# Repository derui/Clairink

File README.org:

* Clairink
This is a split keyboard having these features:

- ZMK firmware
- 3D printed keyboard case & Rotally encoder nob
  - You can manage behavior with ZMK
- Focus Thocky sound with the Lofree's Phantom switch
- all wireless
- able to use rechageable AAA battery x2
  - I use eneloop for this

* Bill Of Materials

| Name                                   | Qty |
|----------------------------------------+-----|
| SeeedStudio XIAO nRF52480              |   2 |
| AAA battery holder                     |   4 |
| M2 nut                                 |  12 |
| M2 screw                               |  12 |
| AE-XCL102D333CR-G                      |   2 |
| 1N4148W                                |  64 |
| Choc V2 Socket                         |  42 |
| Rotally Encoder (ALPS EC12 compatible) |   2 |
| SS-12D01G3                             |   2 |
| chip condenser (0.1uF)                 |   4 |
| chip register (2.2KΩ)                  |   4 |

* LICENSE
MIT

** LICENSE note
This keyboard uses Seeed Studio's XIAO nRF52480 kicad symbol and footprint. There are licensed under MIT that they written in [[https://wiki.seeedstudio.com/ja/License/][here]].

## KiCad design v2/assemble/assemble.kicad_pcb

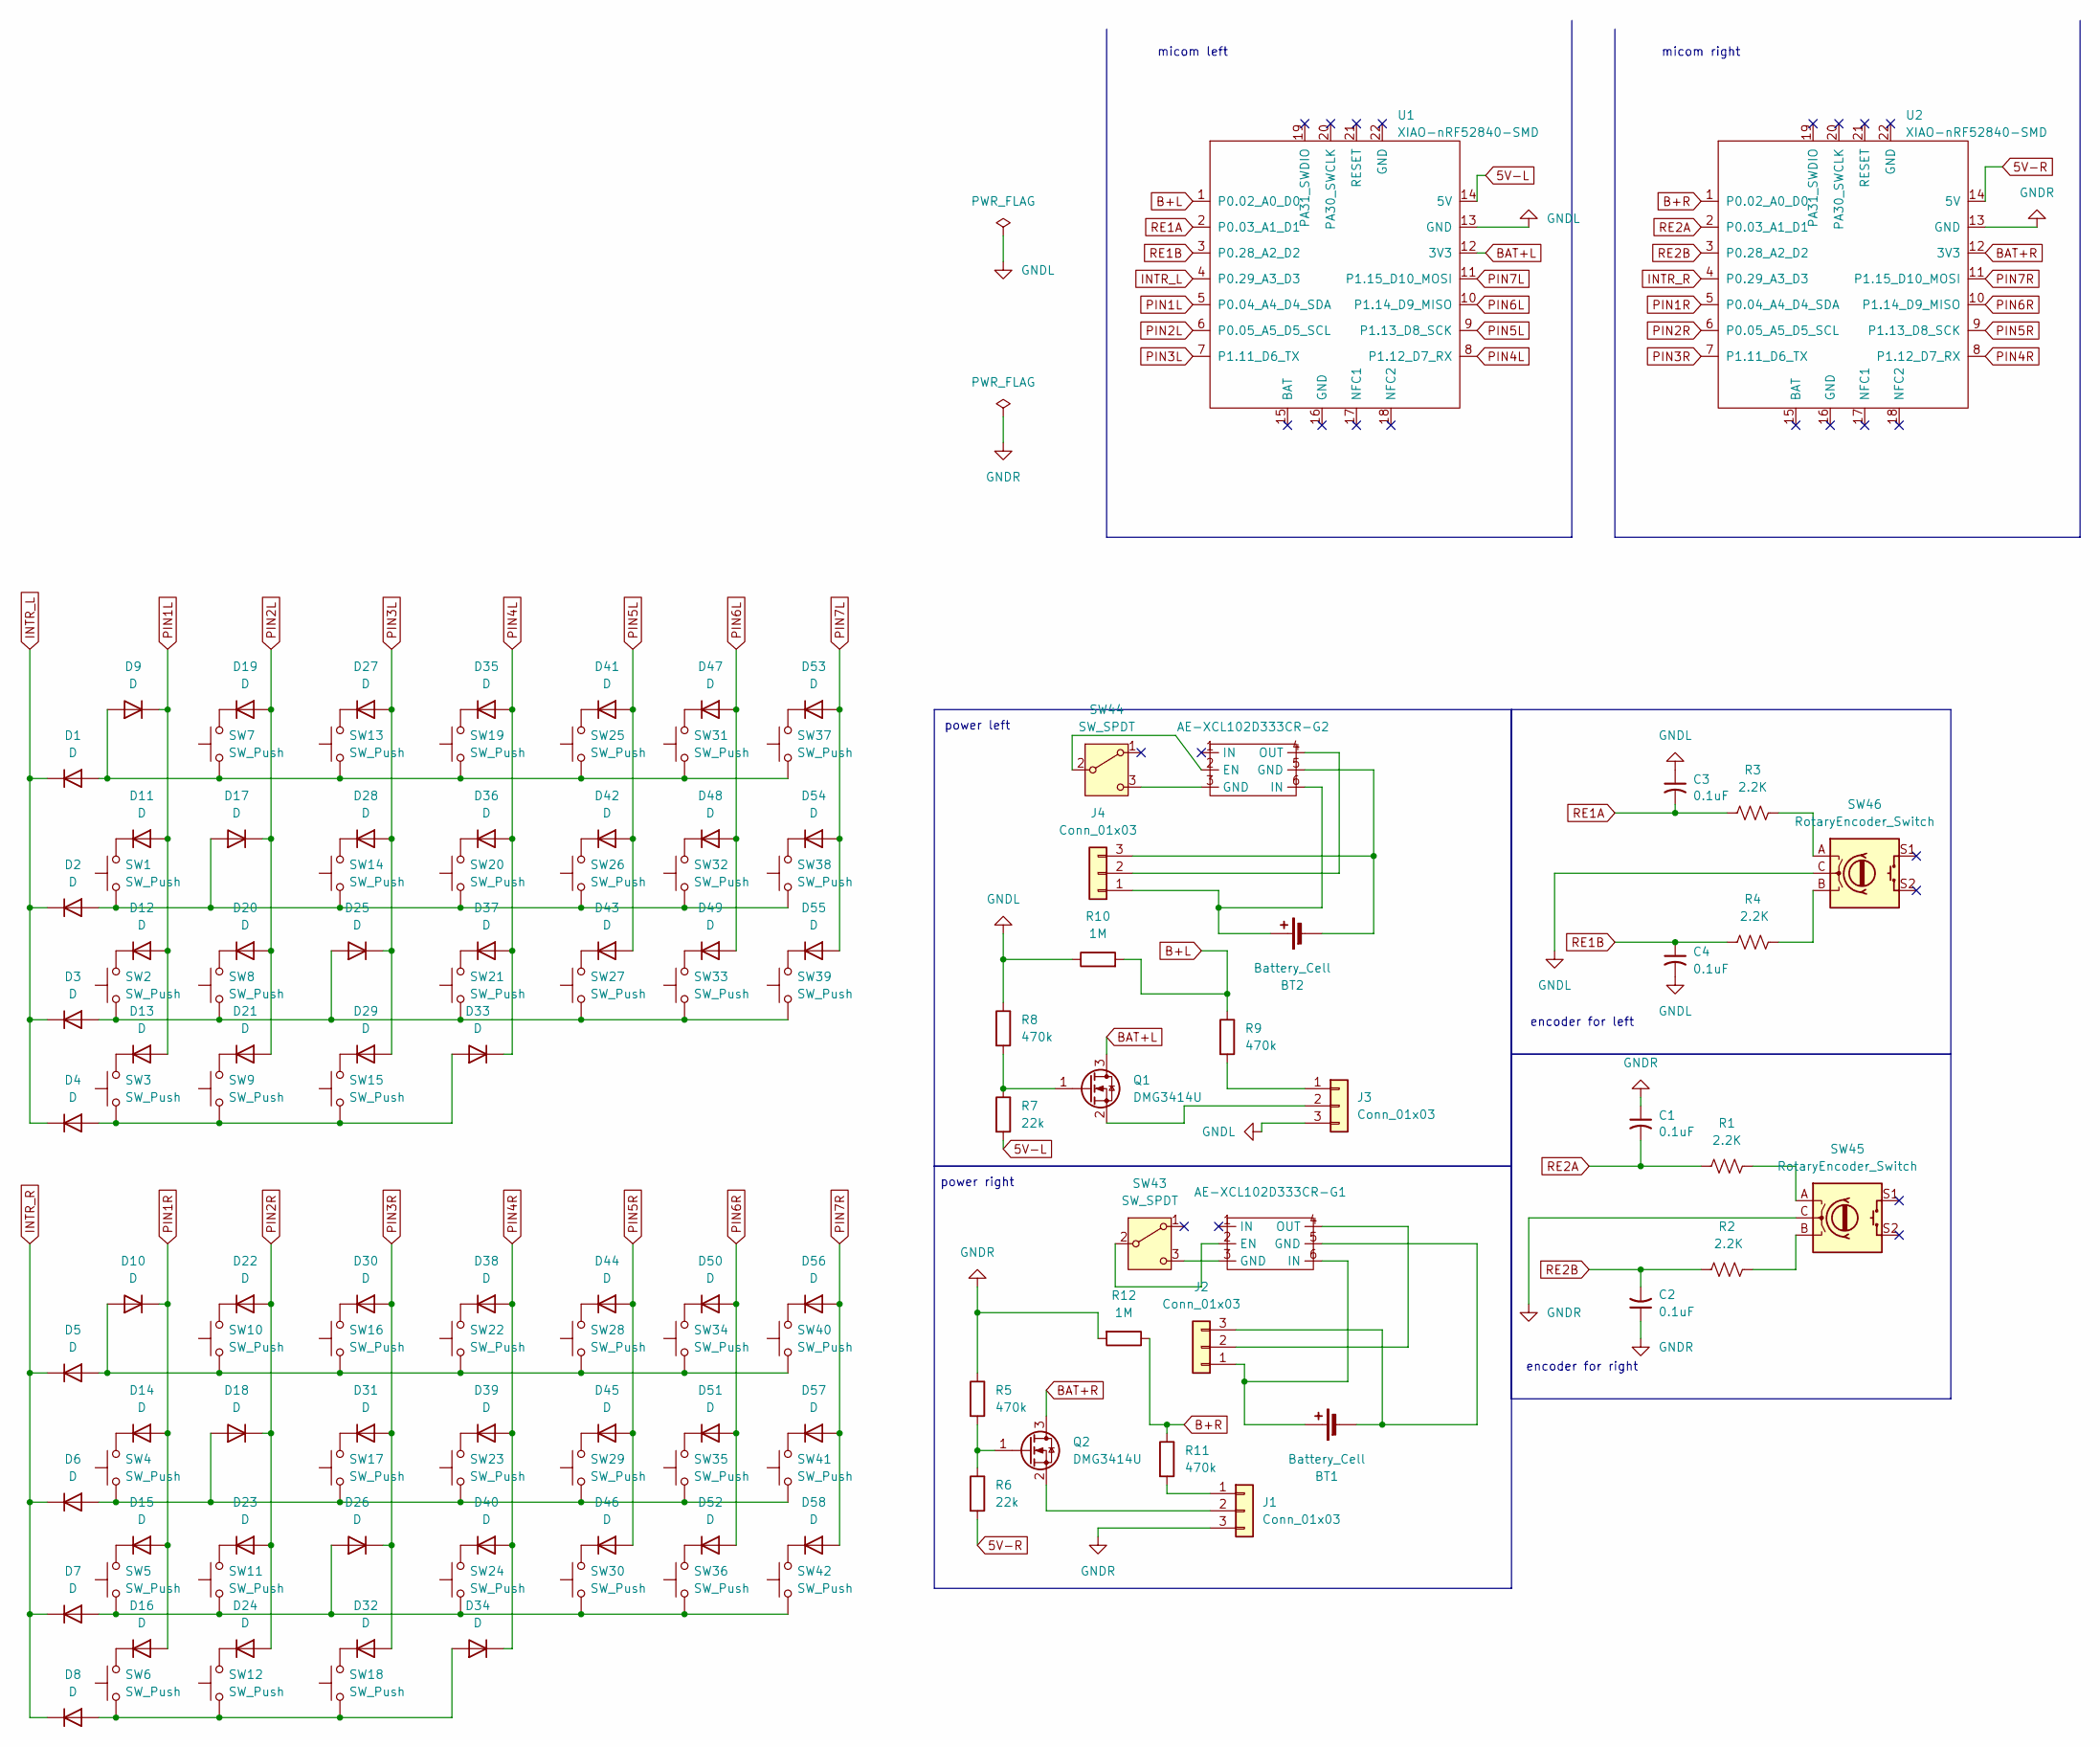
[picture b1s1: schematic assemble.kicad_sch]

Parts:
AE-XCL102D333CR-G1, AE-XCL102D333CR-G2: AE-XCL102D333CR-G
BT1, BT2: Battery_Cell; Battery_AAA
C1, C2, C3, C4: 0.1uF; C_0603_1608Metric_Pad1.08x0.95mm_HandSolder
D1, D2, D3, D4, D5, D6, D7, D8, D9, D10, D11, D12, D13, D14, D15, D16, D17, D18, D19, D20, D21, D22, D23, D24, D25, D26, D27, D28, D29, D30, D31, D32, D33, D34, D35, D36, D37, D38, D39, D40, D41, D42, D43, D44, D45, D46, D47, D48, D49, D50, D51, D52, D53, D54, D55, D56, D57, D58: D; Diode_SMD
J1, J2, J3, J4: Conn_01x03; JST_ZH_B3B-ZR_1x03_P1.50mm_Vertical
Q1, Q2: DMG3414U; SOT-23
R1, R2, R3, R4: 2.2K; R_0805_2012Metric_Pad1.20x1.40mm_HandSolder
R5, R8, R9, R11: 470k; R_0805_2012Metric_Pad1.20x1.40mm_HandSolder
R6, R7: 22k; R_0805_2012Metric_Pad1.20x1.40mm_HandSolder
R10, R12: 1M; R_0805_2012Metric_Pad1.20x1.40mm_HandSolder
SW1, SW2, SW3, SW4, SW5, SW6, SW7, SW8, SW9, SW10, SW11, SW12, SW13, SW14, SW15, SW16, SW17, SW18, SW19, SW20, SW21, SW22, SW23, SW24, SW25, SW26, SW27, SW28, SW29, SW30, SW31, SW32, SW33, SW34, SW35, SW36, SW37, SW38, SW39, SW40, SW41, SW42: SW_Push; Choc_v2_Hotswap_1u_16.6
SW43, SW44: SW_SPDT; TGSW_MSK-12D19
SW45, SW46: RotaryEncoder_Switch; RotaryEncoder_EC12E
U1, U2: XIAO-nRF52840-SMD

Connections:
5V-L: R7.2, U1.14 (5V)
5V-R: R6.2, U2.14 (5V)
B+L: R9.1, R10.2, U1.1 (P0.02_A0_D0)
B+R: R11.1, R12.1, U2.1 (P0.02_A0_D0)
BAT+L: Q1.3 (D), U1.12 (3V3)
BAT+R: Q2.3 (D), U2.12 (3V3)
GNDL: C3.1, C4.2, J3.3, R8.1, R10.1, SW46.C, U1.13 (GND)
GNDR: C1.1, C2.1, J1.3, R5.1, R12.2, SW45.C, U2.13 (GND)
INTR_L: D1.1 (K), D2.1 (K), D3.1 (K), D4.1 (K), U1.4 (P0.29_A3_D3)
INTR_R: D5.1 (K), D6.1 (K), D7.1 (K), D8.1 (K), U2.4 (P0.29_A3_D3)
unnamed: AE-XCL102D333CR-G1.2 (EN), SW43.2 (B)
unnamed: AE-XCL102D333CR-G1.4 (OUT), J2.2
unnamed: AE-XCL102D333CR-G2.2 (EN), SW44.2 (B)
unnamed: AE-XCL102D333CR-G2.4 (OUT), J4.2
unnamed: AE-XCL102D333CR-G1.6 (IN), BT1.1 (+), J2.1
unnamed: AE-XCL102D333CR-G1.5 (GND), BT1.2 (-), J2.3
unnamed: AE-XCL102D333CR-G2.6 (IN), BT2.1 (+), J4.1
unnamed: AE-XCL102D333CR-G2.5 (GND), BT2.2 (-), J4.3
unnamed: D1.2 (A), D9.2 (A), SW7.1, SW13.1, SW19.1, SW25.1, SW31.1, SW37.1
unnamed: D5.2 (A), D10.2 (A), SW10.1, SW16.1, SW22.1, SW28.1, SW34.1, SW40.1
unnamed: D11.1 (K), SW1.2
unnamed: D12.1 (K), SW2.2
unnamed: D13.1 (K), SW3.2
unnamed: D14.1 (K), SW4.2
unnamed: D15.1 (K), SW5.2
unnamed: D16.1 (K), SW6.2
unnamed: D2.2 (A), D17.2 (A), SW1.1, SW14.1, SW20.1, SW26.1, SW32.1, SW38.1
unnamed: D6.2 (A), D18.2 (A), SW4.1, SW17.1, SW23.1, SW29.1, SW35.1, SW41.1
unnamed: D19.1 (K), SW7.2
unnamed: D20.1 (K), SW8.2
unnamed: D21.1 (K), SW9.2
unnamed: D22.1 (K), SW10.2
unnamed: D23.1 (K), SW11.2
unnamed: D24.1 (K), SW12.2
unnamed: D3.2 (A), D25.2 (A), SW2.1, SW8.1, SW21.1, SW27.1, SW33.1, SW39.1
unnamed: D7.2 (A), D26.2 (A), SW5.1, SW11.1, SW24.1, SW30.1, SW36.1, SW42.1
unnamed: D27.1 (K), SW13.2
unnamed: D28.1 (K), SW14.2
unnamed: D29.1 (K), SW15.2
unnamed: D30.1 (K), SW16.2
unnamed: D31.1 (K), SW17.2
unnamed: D32.1 (K), SW18.2
unnamed: D4.2 (A), D33.2 (A), SW3.1, SW9.1, SW15.1
unnamed: D8.2 (A), D34.2 (A), SW6.1, SW12.1, SW18.1
unnamed: D35.1 (K), SW19.2
unnamed: D36.1 (K), SW20.2
unnamed: D37.1 (K), SW21.2
unnamed: D38.1 (K), SW22.2
unnamed: D39.1 (K), SW23.2
unnamed: D40.1 (K), SW24.2
unnamed: D41.1 (K), SW25.2
unnamed: D42.1 (K), SW26.2
unnamed: D43.1 (K), SW27.2
unnamed: D44.1 (K), SW28.2
unnamed: D45.1 (K), SW29.2
unnamed: D46.1 (K), SW30.2
unnamed: D47.1 (K), SW31.2
unnamed: D48.1 (K), SW32.2
unnamed: D49.1 (K), SW33.2
unnamed: D50.1 (K), SW34.2
unnamed: D51.1 (K), SW35.2
unnamed: D52.1 (K), SW36.2
unnamed: D53.1 (K), SW37.2
unnamed: D54.1 (K), SW38.2
unnamed: D55.1 (K), SW39.2
unnamed: D56.1 (K), SW40.2
unnamed: D57.1 (K), SW41.2
unnamed: D58.1 (K), SW42.2
unnamed: J1.1, R11.2
unnamed: J1.2, Q2.2 (S)
unnamed: J3.1, R9.2
unnamed: J3.2, Q1.2 (S)
unnamed: Q1.1 (G), R7.1, R8.2
unnamed: Q2.1 (G), R5.2, R6.1
unnamed: R1.2, SW45.A
unnamed: R2.2, SW45.B
unnamed: R3.2, SW46.A
unnamed: R4.2, SW46.B
unnamed: AE-XCL102D333CR-G1.3 (GND), SW43.3 (C)
unnamed: AE-XCL102D333CR-G2.3 (GND), SW44.3 (C)
PIN1L: D9.1 (K), D11.2 (A), D12.2 (A), D13.2 (A), U1.5 (P0.04_A4_D4_SDA)
PIN1R: D10.1 (K), D14.2 (A), D15.2 (A), D16.2 (A), U2.5 (P0.04_A4_D4_SDA)
PIN2L: D17.1 (K), D19.2 (A), D20.2 (A), D21.2 (A), U1.6 (P0.05_A5_D5_SCL)
PIN2R: D18.1 (K), D22.2 (A), D23.2 (A), D24.2 (A), U2.6 (P0.05_A5_D5_SCL)
PIN3L: D25.1 (K), D27.2 (A), D28.2 (A), D29.2 (A), U1.7 (P1.11_D6_TX)
PIN3R: D26.1 (K), D30.2 (A), D31.2 (A), D32.2 (A), U2.7 (P1.11_D6_TX)
PIN4L: D33.1 (K), D35.2 (A), D36.2 (A), D37.2 (A), U1.8 (P1.12_D7_RX)
PIN4R: D34.1 (K), D38.2 (A), D39.2 (A), D40.2 (A), U2.8 (P1.12_D7_RX)
PIN5L: D41.2 (A), D42.2 (A), D43.2 (A), U1.9 (P1.13_D8_SCK)
PIN5R: D44.2 (A), D45.2 (A), D46.2 (A), U2.9 (P1.13_D8_SCK)
PIN6L: D47.2 (A), D48.2 (A), D49.2 (A), U1.10 (P1.14_D9_MISO)
PIN6R: D50.2 (A), D51.2 (A), D52.2 (A), U2.10 (P1.14_D9_MISO)
PIN7L: D53.2 (A), D54.2 (A), D55.2 (A), U1.11 (P1.15_D10_MOSI)
PIN7R: D56.2 (A), D57.2 (A), D58.2 (A), U2.11 (P1.15_D10_MOSI)
RE1A: C3.2, R3.1, U1.2 (P0.03_A1_D1)
RE1B: C4.1, R4.1, U1.3 (P0.28_A2_D2)
RE2A: C1.2, R1.1, U2.2 (P0.03_A1_D1)
RE2B: C2.2, R2.1, U2.3 (P0.28_A2_D2)

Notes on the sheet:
encoder for right
encoder for left
micom right
power left
power right
micom left

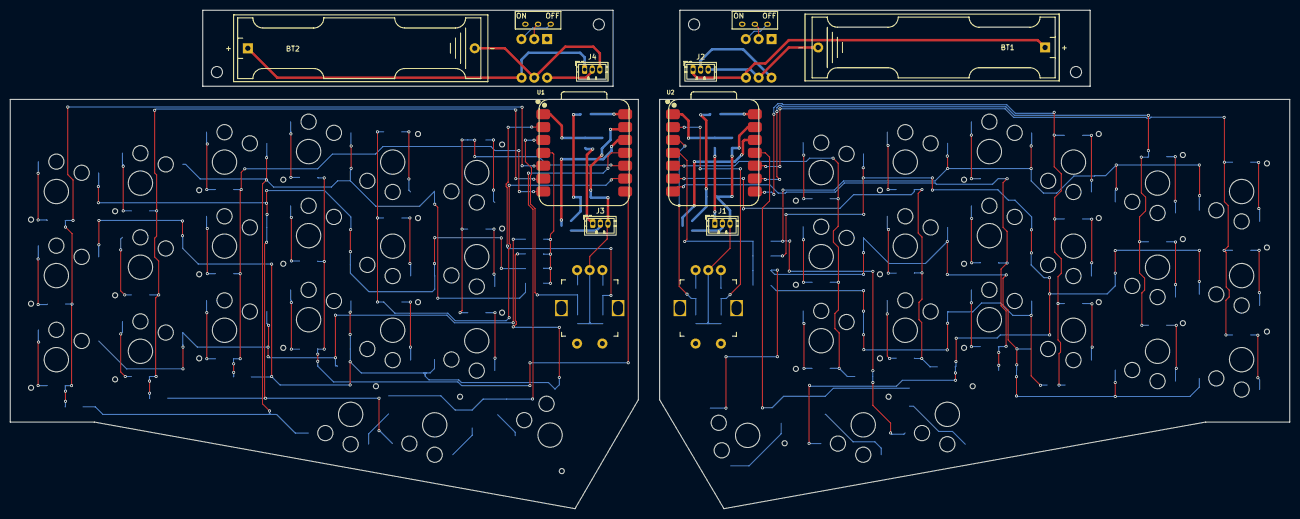
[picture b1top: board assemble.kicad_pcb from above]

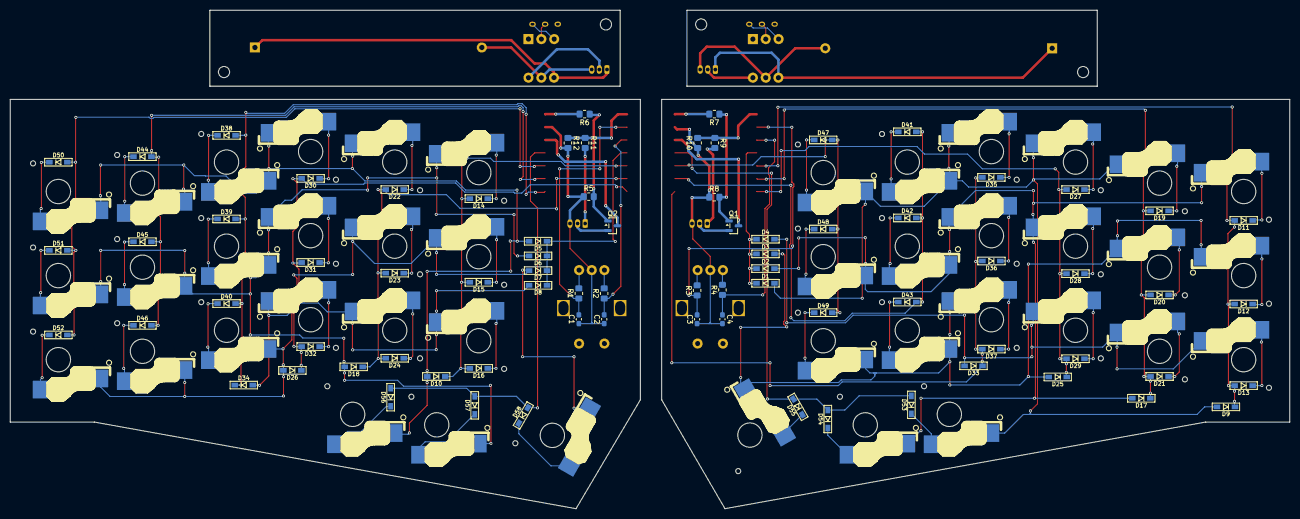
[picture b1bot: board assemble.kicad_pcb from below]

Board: 2 copper layers, 252.6 x 98.4 mm, 136 parts (18 on the bottom side), 98 nets.

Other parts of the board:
Ref**: Val**; m2_Screw_Hole
Ref**#2, Ref**#3, Ref**#4: Val**; m2_Screw_Hole

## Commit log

2026-03-08 feat: readme and base assembles
2026-03-09 feat: add some rotary encoder
2026-03-15 wip: implement PCB
2026-03-19 fix: move pcb
2026-03-23 fix: add screw hole
2026-03-27 chore: update flake
2026-03-29 fix: typo
2026-04-01 feat: add case base
2026-04-05 feat: add switch plate
2026-04-05 fix: add GND pattern
2026-04-05 fix: rename
2026-04-14 feat: update kicad
2026-05-13 feat: add v1.2 and v1.3
2026-05-16 refactor: move files
2026-05-16 docs: Update README with component changes
2026-05-24 chore: update flake lock file dependencies
    Updates the nixpkgs reference in flake.lock to use
    the latest known stable commit hash.
2026-05-24 feat: implement v2 assemble
2026-06-05 chore: update flake lock file hashes
2026-06-05 feat: update some pins
2026-06-07 feat: finalize v2
